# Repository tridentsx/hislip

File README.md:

# hislip

A native Go implementation of HiSLIP, the IVI High-Speed LAN Instrument
Protocol, for the [GoTMC][gotmc] test and measurement stack.

HiSLIP is specified by [IVI-6.1][ivi61], revision 2.0. It is the LXI-era
replacement for VXI-11 and requires no ONC/Sun RPC.

## Status

Early development. Milestone 0 of the design specification, the protocol codec,
is implemented and its exit criterion is met: the decoder is fuzzed, and the
data path is asserted to perform no heap allocation.

The server is next, before the client. That inverts the milestone numbering
deliberately — no HiSLIP-capable instrument is available on the development
bench, so a finished client would have nothing to talk to, whereas a finished
server can be driven immediately by NI-VISA, Keysight IO Libraries, pyvisa-py
and `lxi-tools/libhislip`. The reasoning is recorded under "Execution order" in
Part IV of the specification.

Conformance is established against independent implementations rather than
against this project's own two halves, which would agree with each other whether
or not they agree with IVI-6.1.

The design specification lives at
[docs/design-spec.md in tridentsx/tmc-gateway][design-spec], since it is a
single document covering this library (Part I), the PoE-to-GPIB adapter
hardware (Part II), and its TinyGo firmware (Part III) together, plus
milestones/acceptance-criteria/risk sections that cut across all three —
splitting it would have broken that traceability. Section references in this
repository's source comments, such as "§5.1", refer to it there. The hardware
design and firmware themselves also moved to `tmc-gateway`, along with the
KiCad netlist-verification tooling that supports them; this repository is now
the library alone.

This repository lives at `github.com/tridentsx/hislip` for now, not yet part
of the `gotmc` organisation. It was originally developed against the module
path `github.com/gotmc/hislip` on the assumption that no upstream repository
would need to exist yet — but a module's declared path has to match where
it's actually fetched from for `go get` to work at all, so it's renamed here
to the path it's really hosted at. The intent to offer this to `gotmc` once
it's finished hasn't changed; that will mean one real import-path rewrite
when/if it happens, not zero.

## Layout

```text
protocol/          wire format: header codec, message types, error codes,
                   MessageID arithmetic, version negotiation
server/            session state machine and the Device interface
client/            desktop client
extension/gotmc/   optional vendor extension for explicit reads
```

The `protocol` and `server` packages are the device side. They compile under
TinyGo for microcontroller firmware, which imposes two rules:

- imports are restricted to a small, verified subset of the standard library;
- the caller supplies every buffer, and the data path does not allocate.

Both rules exist because the same code runs on a Raspberry Pi RP2350 with a
cooperatively scheduled runtime and a stop-the-world garbage collector, where an
allocation in the data path can stall a timing-sensitive bus transfer.

The import boundary is enforced rather than merely documented. `TestDeviceImportGraph`
in the root package walks the transitive import graph of the device-side
packages and fails on anything outside an allowlist. The realistic failure is
not a deliberate bad import but an `fmt.Errorf` added to an error path long
after the boundary was agreed.

## Two rules worth knowing before reading the code

**Never size a buffer from the wire.** The header's payload length field is 64
bits wide and is supplied by the peer. `make([]byte, header.Length)` is a
denial-of-service vector on an unauthenticated TCP port. Use
`protocol.CheckLength` against the negotiated maximum, then stream through a
fixed scratch buffer with `protocol.ReadPayload`.

**Decoding is permissive on purpose.** `protocol.DecodeHeader` validates the
prologue and nothing else. A receiver has to be able to decode a header it
intends to reject, so that it can consume the payload and stay synchronised with
the peer. Acceptance decisions belong to the session layer, using
`MessageType.Defined`, `MessageType.Reserved`, `MessageType.LegalOn`,
`MessageType.MinVersion` and `CheckLength`.

## Testing

```sh
go test ./...
go test ./... -race -cover
go test ./protocol -run '^$' -fuzz=FuzzDecodeHeader -fuzztime=60s
```

Conformance vectors live in [internal/vectors](internal/vectors) as data files
rather than as Go literals, so that the same corpus can drive a firmware test
harness or an implementation in another language. They are written out by hand
from IVI-6.1, never generated by the code under test, so a coding error in the
codec cannot be masked by the same error in the expectation. The message type
table is transcribed twice for the same reason — once in
`protocol/constants.go` and once in `protocol/constants_test.go` — so that a
transcription error has to be made identically in both places to go unnoticed.

Three fuzz targets cover the decoder, the payload reader and the message
framing. `FuzzDecodeHeader` checks more than the absence of panics: any input
that decodes successfully must re-encode to exactly the bytes it came from,
which is what catches a wrong field offset or a byte-order mistake that a fixed
set of vectors can miss.

`TestCodecDoesNotAllocate` asserts that the data path performs no heap
allocation. This is a timing requirement rather than a memory one. The same code
runs on an RP2350 whose garbage collector stops both cores, so an allocation
during a transfer can stall a GPIB handshake, and a spurious handshake timeout
presents to the user as a bus fault. The assertions are excluded from race
builds, because the race detector allocates on its own account.

## Interoperability

Unit tests confirm the implementation does what its author intended. Only an
independent implementation confirms the intention was right, so conformance is
established against clients this project did not write:

```sh
./interop/run.sh
```

Three independent clients currently drive the example server — pyvisa-py,
PyHiSLIP and `lxi-tools/libhislip` — for 32 checks with no failures. Clients that
are not installed are skipped rather than failed.

Between them they have found three defects that a full unit suite did not, and
they settled the one open protocol question in the design specification: IVI-6.1
Table 4 lists `DeviceClearAcknowledge` on the asynchronous channel, and two
independent clients read it from the synchronous one, agreeing with the
transaction description instead.

Coverage, procedure, findings and the limitations of each client are recorded in
[interop/README.md](interop/README.md).

## A defect in IVI-6.1

Table 4 lists `DeviceClearAcknowledge`, message type 9, as an asynchronous
message. The Device Clear transaction description in section 6.12 contradicts
this: step 7 of the client procedure reads "Wait for the server to respond with
DeviceClearAcknowledge on the synchronous channel", and the message summary
table also gives the channel as synchronous.

This implementation follows the transaction description and treats the message
as synchronous. See `TestDeviceClearAcknowledgeChannel`. The intent is to
confirm the behaviour against independent third-party HiSLIP clients before the
server is released.

## Licence

MIT. See [LICENSE.txt](LICENSE.txt).

[design-spec]: https://github.com/tridentsx/tmc-gateway/blob/main/docs/design-spec.md
[gotmc]: https://github.com/gotmc
[ivi61]: https://www.ivifoundation.org/downloads/Protocol%20Specifications/IVI-6.1_HiSLIP-2.0-2020-04-23.pdf

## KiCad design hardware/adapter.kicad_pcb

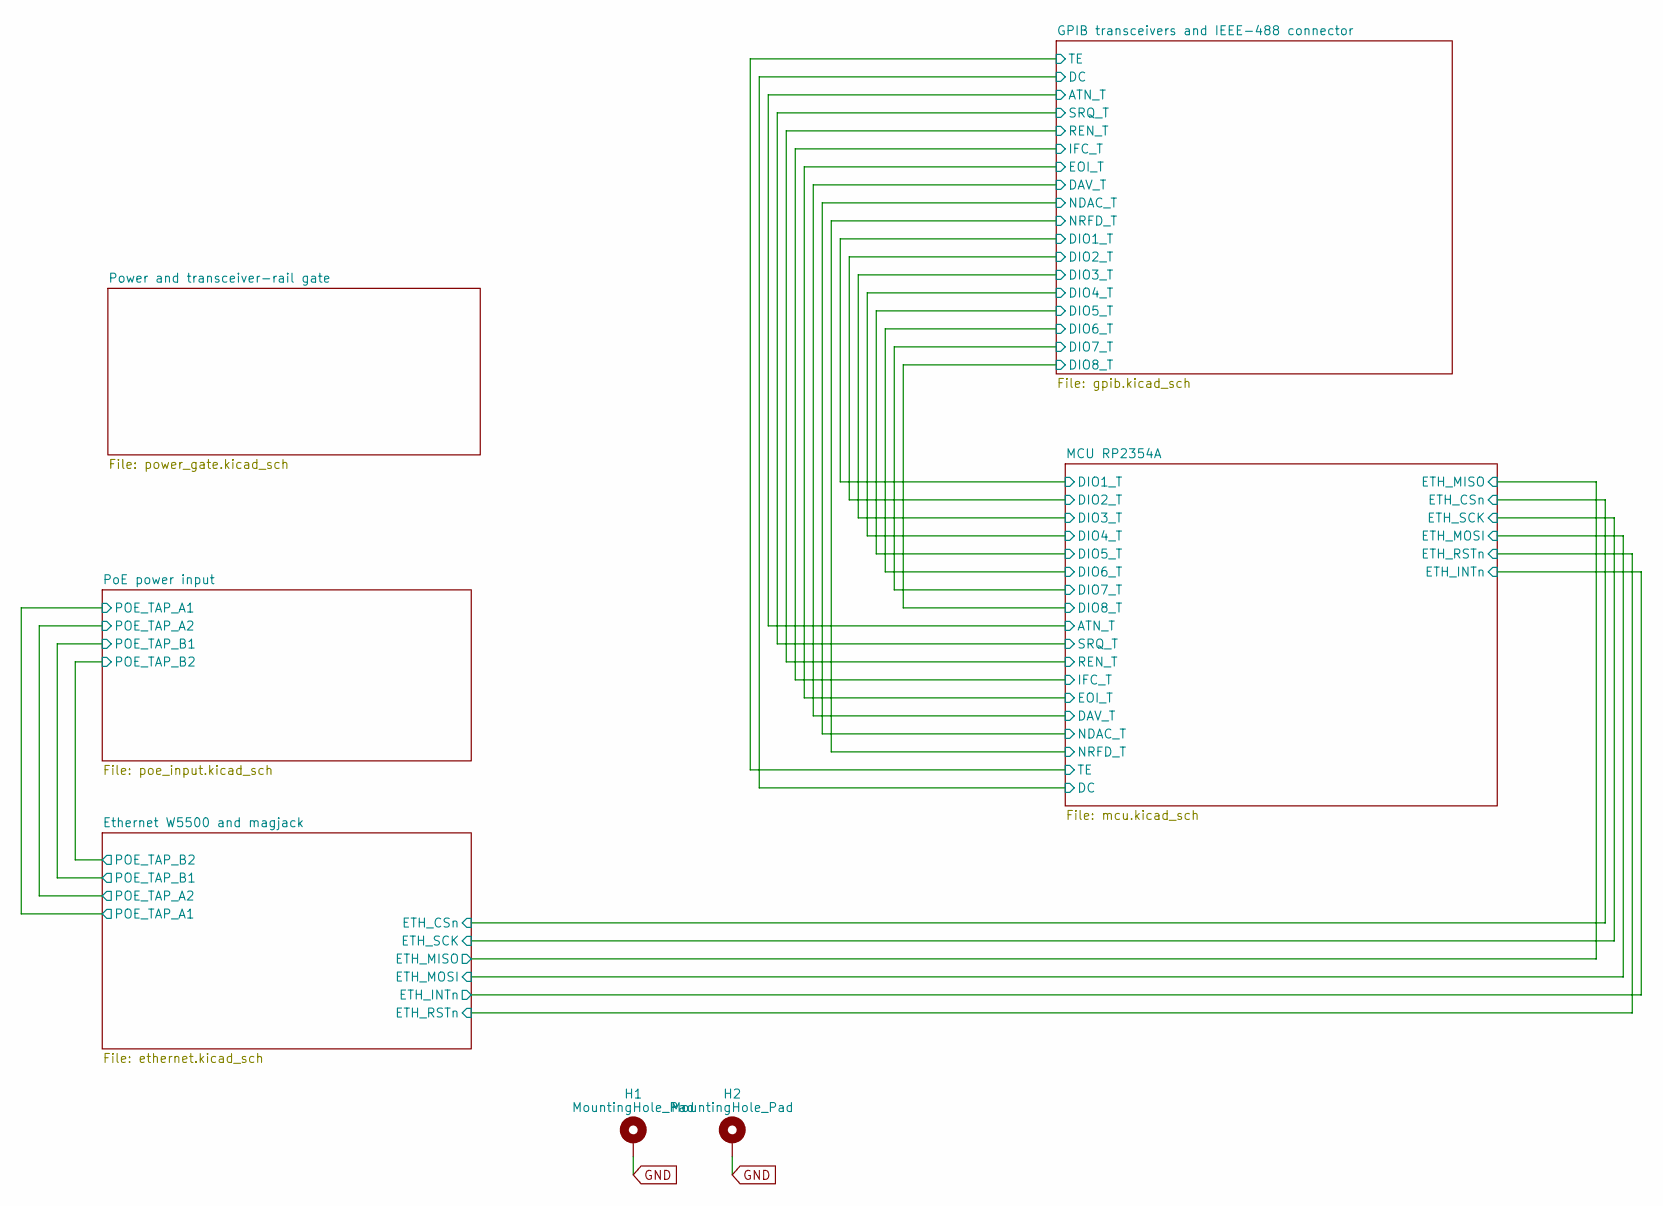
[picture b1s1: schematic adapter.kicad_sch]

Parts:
H1, H2: MountingHole_Pad; MountingHole_3.2mm_M3_Pad

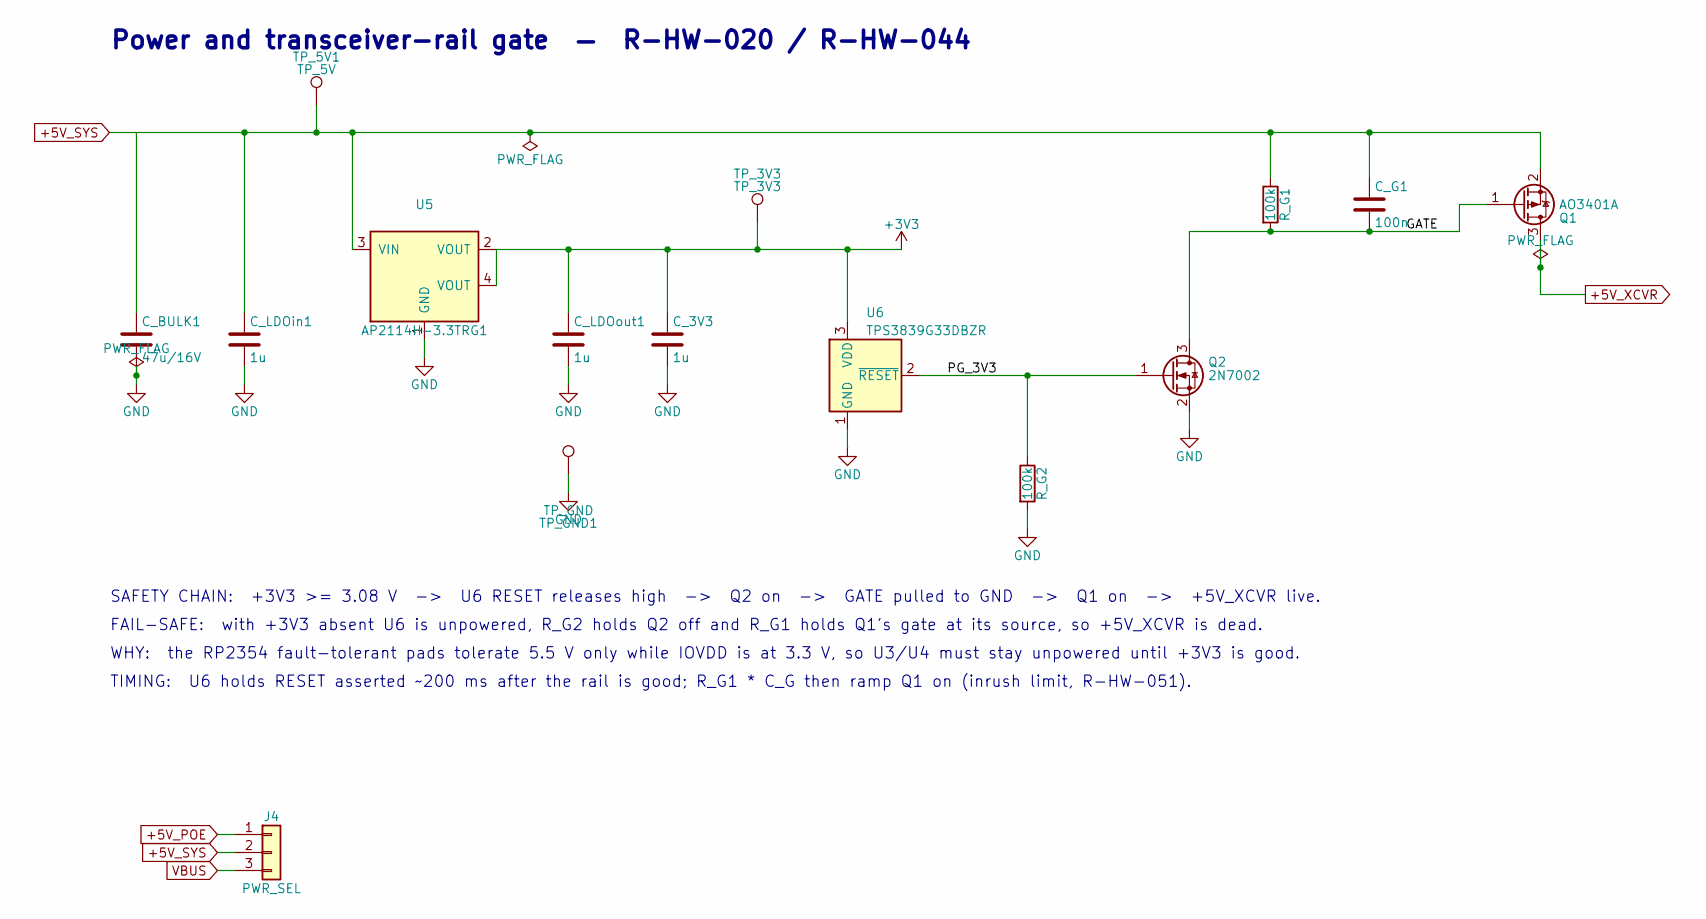
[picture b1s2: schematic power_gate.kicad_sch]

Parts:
C_3V3: 1u; C_0805_2012Metric
C_BULK1: 47u/16V; C_1206_3216Metric
C_G1: 100n; C_0805_2012Metric
C_LDOin1: 1u; C_0805_2012Metric
C_LDOout1: 1u; C_0805_2012Metric
J4: PWR_SEL; PinHeader_1x03_P2.54mm_Vertical
Q1: AO3401A; SOT-23
Q2: 2N7002; SOT-23
R_G1, R_G2: 100k; R_0805_2012Metric
TP_3V3: TP_3V3; TestPoint_Pad_D1.5mm
TP_5V1: TP_5V; TestPoint_Pad_D1.5mm
TP_GND1: TP_GND; TestPoint_Pad_D1.5mm
U5: AP2114H-3.3TRG1; SOT-223_L6.7-W3.5-P2.30-BR
U6: TPS3839G33DBZR; SOT-23

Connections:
+3V3: C_3V3.1, C_LDOout1.1, TP_3V3.1 (1_1), U5.2 (VOUT), U5.4 (VOUT), U6.3 (VDD); also elsewhere on the board
+5V_POE: J4.1; also elsewhere on the board
/Power and transceiver-rail gate/GATE: C_G1.2, Q1.1 (G), Q2.3 (D), R_G1.2
/Power and transceiver-rail gate/PG_3V3: Q2.1 (G), R_G2.1, U6.2 (~RESET)
VBUS: J4.3; also elsewhere on the board

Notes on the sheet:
FAIL-SAFE: with +3V3 absent U6 is unpowered, R_G2 holds Q2 off and R_G1 holds Q1's gate at its source, so +5V_XCVR is dead.
SAFETY CHAIN: +3V3 >= 3.08 V -> U6 RESET releases high -> Q2 on -> GATE pulled to GND -> Q1 on -> +5V_XCVR live.
TIMING: U6 holds RESET asserted ~200 ms after the rail is good; R_G1 * C_G then ramp Q1 on (inrush limit, R-HW-051).
WHY: the RP2354 fault-tolerant pads tolerate 5.5 V only while IOVDD is at 3.3 V, so U3/U4 must stay unpowered until +3V3 is good.
Power and transceiver-rail gate — R-HW-020 / R-HW-044

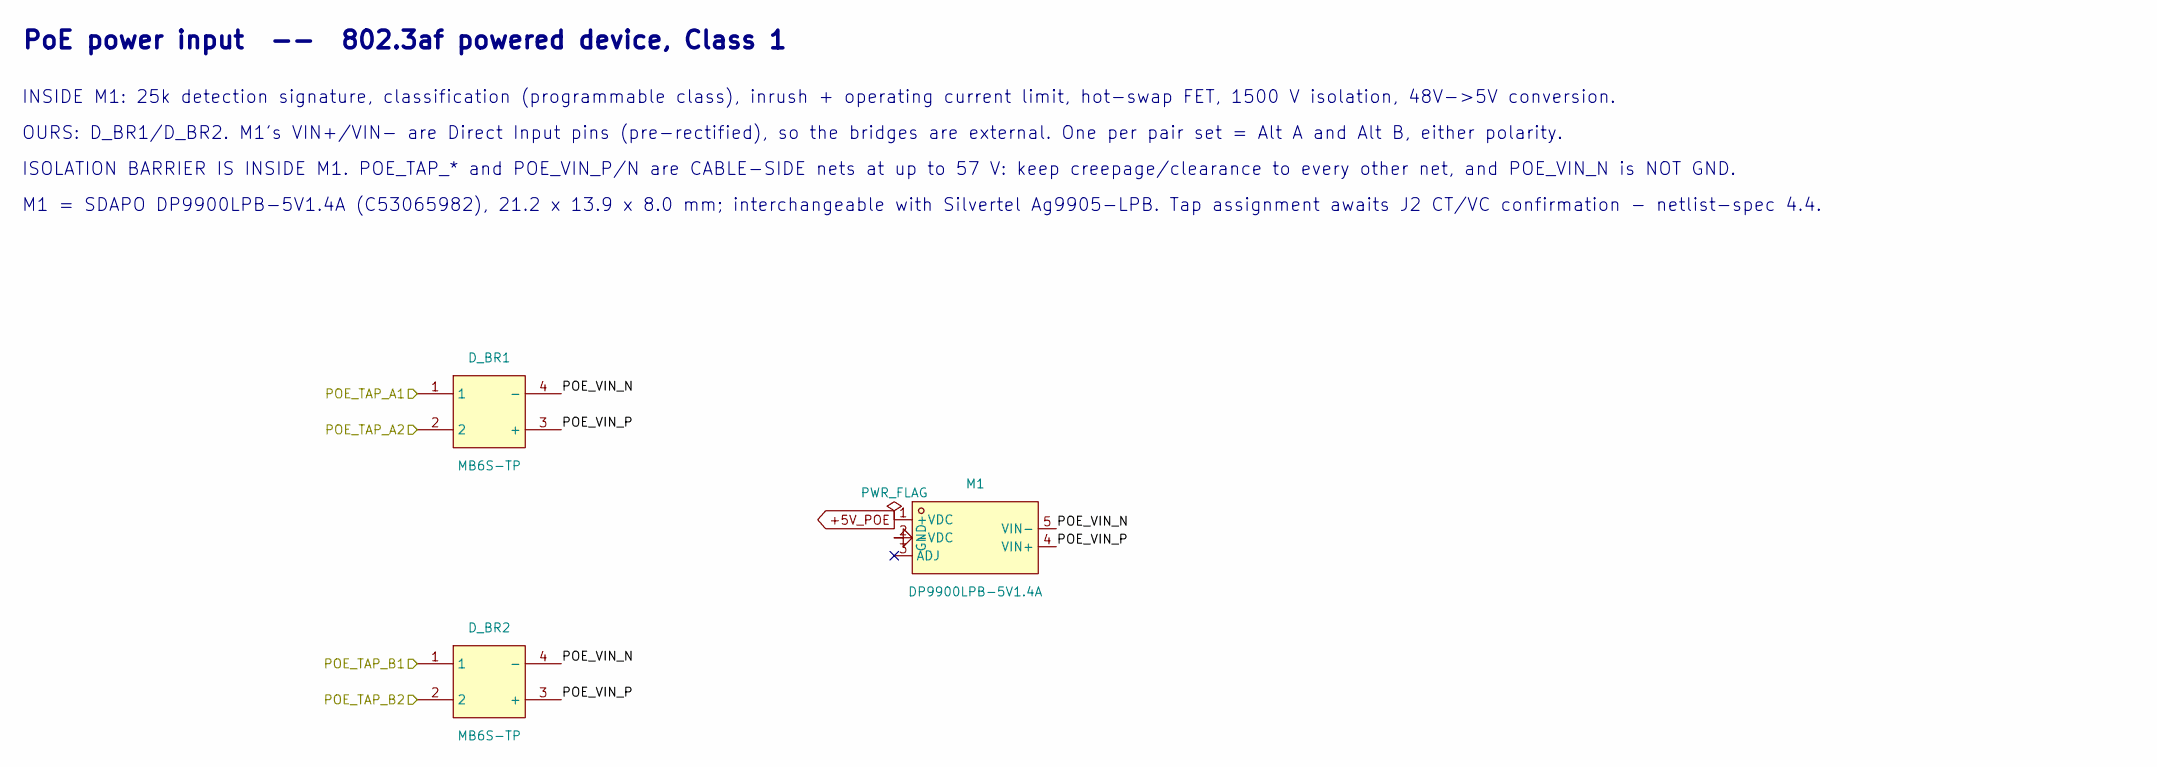
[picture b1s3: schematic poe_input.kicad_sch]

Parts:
D_BR1, D_BR2: MB6S-TP; MBS_L4.7-W4.0-P2.50-LS7.0-TL
M1: DP9900LPB-5V1.4A; COMM-SMD_DP9900LPB-5V1.4A

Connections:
+5V_POE: M1.1 (+VDC); also elsewhere on the board
/Ethernet W5500 and magjack/POE_TAP_A1: D_BR1.1; also elsewhere on the board
/Ethernet W5500 and magjack/POE_TAP_A2: D_BR1.2; also elsewhere on the board
/Ethernet W5500 and magjack/POE_TAP_B1: D_BR2.1; also elsewhere on the board
/Ethernet W5500 and magjack/POE_TAP_B2: D_BR2.2; also elsewhere on the board
/PoE power input/POE_VIN_N: D_BR1.4 (-), D_BR2.4 (-), M1.5 (VIN-)
/PoE power input/POE_VIN_P: D_BR1.3 (+), D_BR2.3 (+), M1.4 (VIN+)

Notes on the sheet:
OURS: D_BR1/D_BR2. M1's VIN+/VIN- are Direct Input pins (pre-rectified), so the bridges are external. One per pair set = Alt A and Alt B, either polarity.
ISOLATION BARRIER IS INSIDE M1. POE_TAP_* and POE_VIN_P/N are CABLE-SIDE nets at up to 57 V: keep creepage/clearance to every other net, and POE_VIN_N is NOT GND.
M1 = SDAPO DP9900LPB-5V1.4A (C53065982), 21.2 x 13.9 x 8.0 mm; interchangeable with Silvertel Ag9905-LPB. Tap assignment awaits J2 CT/VC confirmation - netlist-spec 4.4.
INSIDE M1: 25k detection signature, classification (programmable class), inrush + operating current limit, hot-swap FET, 1500 V isolation, 48V->5V conversion.
PoE power input -- 802.3af powered device, Class 1

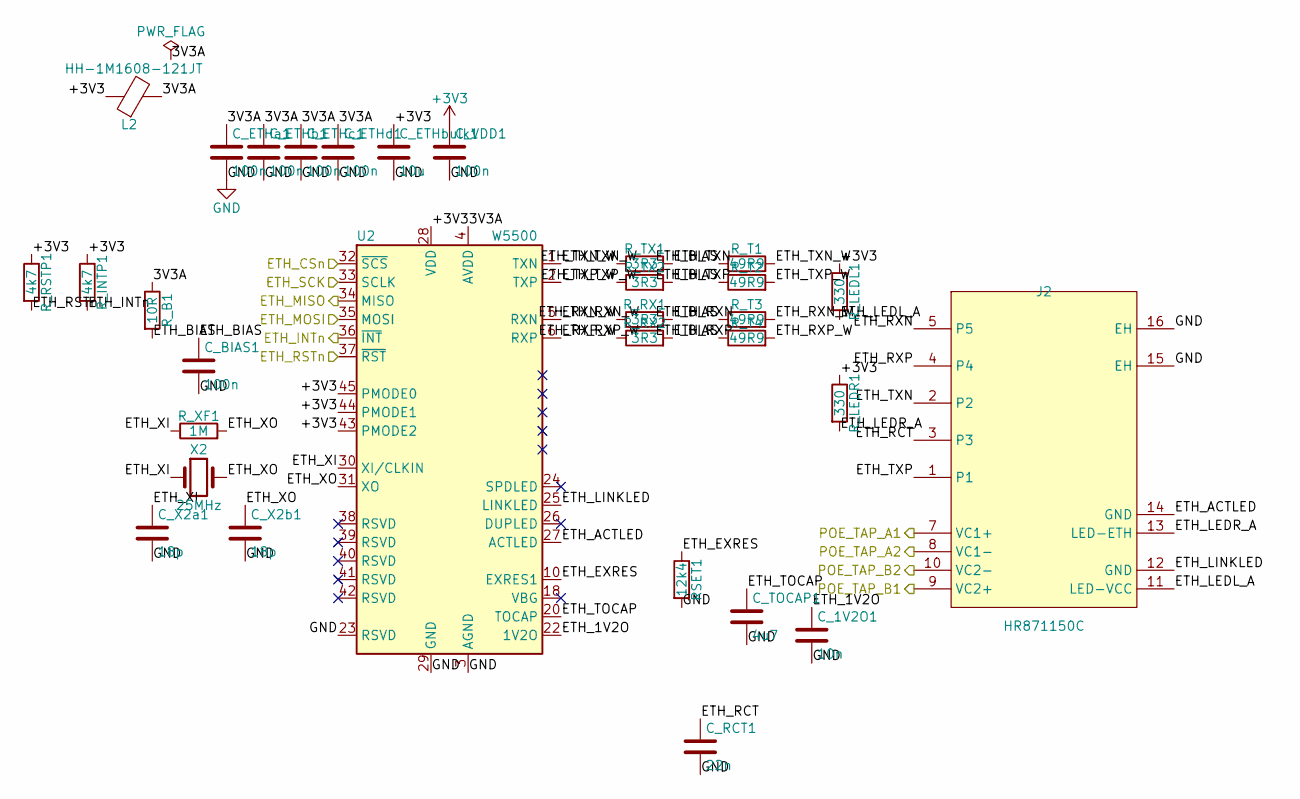
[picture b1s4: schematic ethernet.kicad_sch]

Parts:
C_1V2O1: 10n; C_0805_2012Metric
C_BIAS1: 100n; C_0805_2012Metric
C_ETHa1: 100n; C_0805_2012Metric
C_ETHb1: 100n; C_0805_2012Metric
C_ETHbulk1: 10u; C_0805_2012Metric
C_ETHc1: 100n; C_0805_2012Metric
C_ETHd1: 100n; C_0805_2012Metric
C_RCT1: 22n; C_0805_2012Metric
C_TOCAP1: 4u7; C_0805_2012Metric
C_VDD1: 100n; C_0805_2012Metric
C_X2a1, C_X2b1: 18p; C_0805_2012Metric
J2: HR871150C; RJ45-TH_HR871150C
L2: HH-1M1608-121JT; L_0603_1608Metric
RSET1: 12k4; R_0805_2012Metric
R_B1: 10R; R_0805_2012Metric
R_INTP1: 4k7; R_0805_2012Metric
R_LEDL1: 330; R_0805_2012Metric
R_LEDR1: 330; R_0805_2012Metric
R_RSTP1: 4k7; R_0805_2012Metric
R_RX1, R_RX2: 3R3; R_0805_2012Metric
R_T1, R_T2, R_T3, R_T4: 49R9; R_0805_2012Metric
R_TX1, R_TX2: 3R3; R_0805_2012Metric
R_XF1: 1M; R_0805_2012Metric
U2: W5500; LQFP-48_7x7mm_P0.5mm
X2: 25MHz; Crystal_SMD_3225-4Pin_3.2x2.5mm

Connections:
+3V3: C_ETHbulk1.1, C_VDD1.1, L2.1, R_INTP1.1, R_LEDL1.1, R_LEDR1.1, R_RSTP1.1, U2.28 (VDD), U2.43 (PMODE2), U2.44 (PMODE1), U2.45 (PMODE0); also elsewhere on the board
/Ethernet W5500 and magjack/3V3A: C_ETHa1.1, C_ETHb1.1, C_ETHc1.1, C_ETHd1.1, L2.2, R_B1.1, U2.4 (AVDD), U2.8 (AVDD), U2.11 (AVDD), U2.15 (AVDD), U2.17 (AVDD), U2.21 (AVDD)
/Ethernet W5500 and magjack/ETH_1V2O: C_1V2O1.1, U2.22 (1V2O)
/Ethernet W5500 and magjack/ETH_ACTLED: J2.14 (GND), U2.27 (ACTLED)
/Ethernet W5500 and magjack/ETH_BIAS: C_BIAS1.1, R_B1.2, R_T1.1, R_T2.1, R_T3.1, R_T4.1
/Ethernet W5500 and magjack/ETH_CSn: U2.32 (~SCS); also elsewhere on the board
/Ethernet W5500 and magjack/ETH_EXRES: RSET1.1, U2.10 (EXRES1)
/Ethernet W5500 and magjack/ETH_INTn: R_INTP1.2, U2.36 (~INT); also elsewhere on the board
/Ethernet W5500 and magjack/ETH_LEDL_A: J2.11 (LED-VCC), R_LEDL1.2
/Ethernet W5500 and magjack/ETH_LEDR_A: J2.13 (LED-ETH), R_LEDR1.2
/Ethernet W5500 and magjack/ETH_LINKLED: J2.12 (GND), U2.25 (LINKLED)
/Ethernet W5500 and magjack/ETH_MISO: U2.34 (MISO); also elsewhere on the board
/Ethernet W5500 and magjack/ETH_MOSI: U2.35 (MOSI); also elsewhere on the board
/Ethernet W5500 and magjack/ETH_RCT: C_RCT1.1, J2.3
/Ethernet W5500 and magjack/ETH_RSTn: R_RSTP1.2, U2.37 (~RST); also elsewhere on the board
/Ethernet W5500 and magjack/ETH_RXN: J2.5, R_RX1.2
/Ethernet W5500 and magjack/ETH_RXN_W: R_RX1.1, R_T3.2, U2.5 (RXN)
/Ethernet W5500 and magjack/ETH_RXP: J2.4, R_RX2.2
/Ethernet W5500 and magjack/ETH_RXP_W: R_RX2.1, R_T4.2, U2.6 (RXP)
/Ethernet W5500 and magjack/ETH_SCK: U2.33 (SCLK); also elsewhere on the board
/Ethernet W5500 and magjack/ETH_TOCAP: C_TOCAP1.1, U2.20 (TOCAP)
/Ethernet W5500 and magjack/ETH_TXN: J2.2, R_TX1.2
/Ethernet W5500 and magjack/ETH_TXN_W: R_T1.2, R_TX1.1, U2.1 (TXN)
/Ethernet W5500 and magjack/ETH_TXP: J2.1, R_TX2.2
/Ethernet W5500 and magjack/ETH_TXP_W: R_T2.2, R_TX2.1, U2.2 (TXP)
/Ethernet W5500 and magjack/ETH_XI: C_X2a1.1, R_XF1.1, U2.30 (XI/CLKIN), X2.1
/Ethernet W5500 and magjack/ETH_XO: C_X2b1.1, R_XF1.2, U2.31 (XO), X2.2
/Ethernet W5500 and magjack/POE_TAP_A1: J2.7 (VC1+); also elsewhere on the board
/Ethernet W5500 and magjack/POE_TAP_A2: J2.8 (VC1-); also elsewhere on the board
/Ethernet W5500 and magjack/POE_TAP_B1: J2.9 (VC2+); also elsewhere on the board
/Ethernet W5500 and magjack/POE_TAP_B2: J2.10 (VC2-); also elsewhere on the board

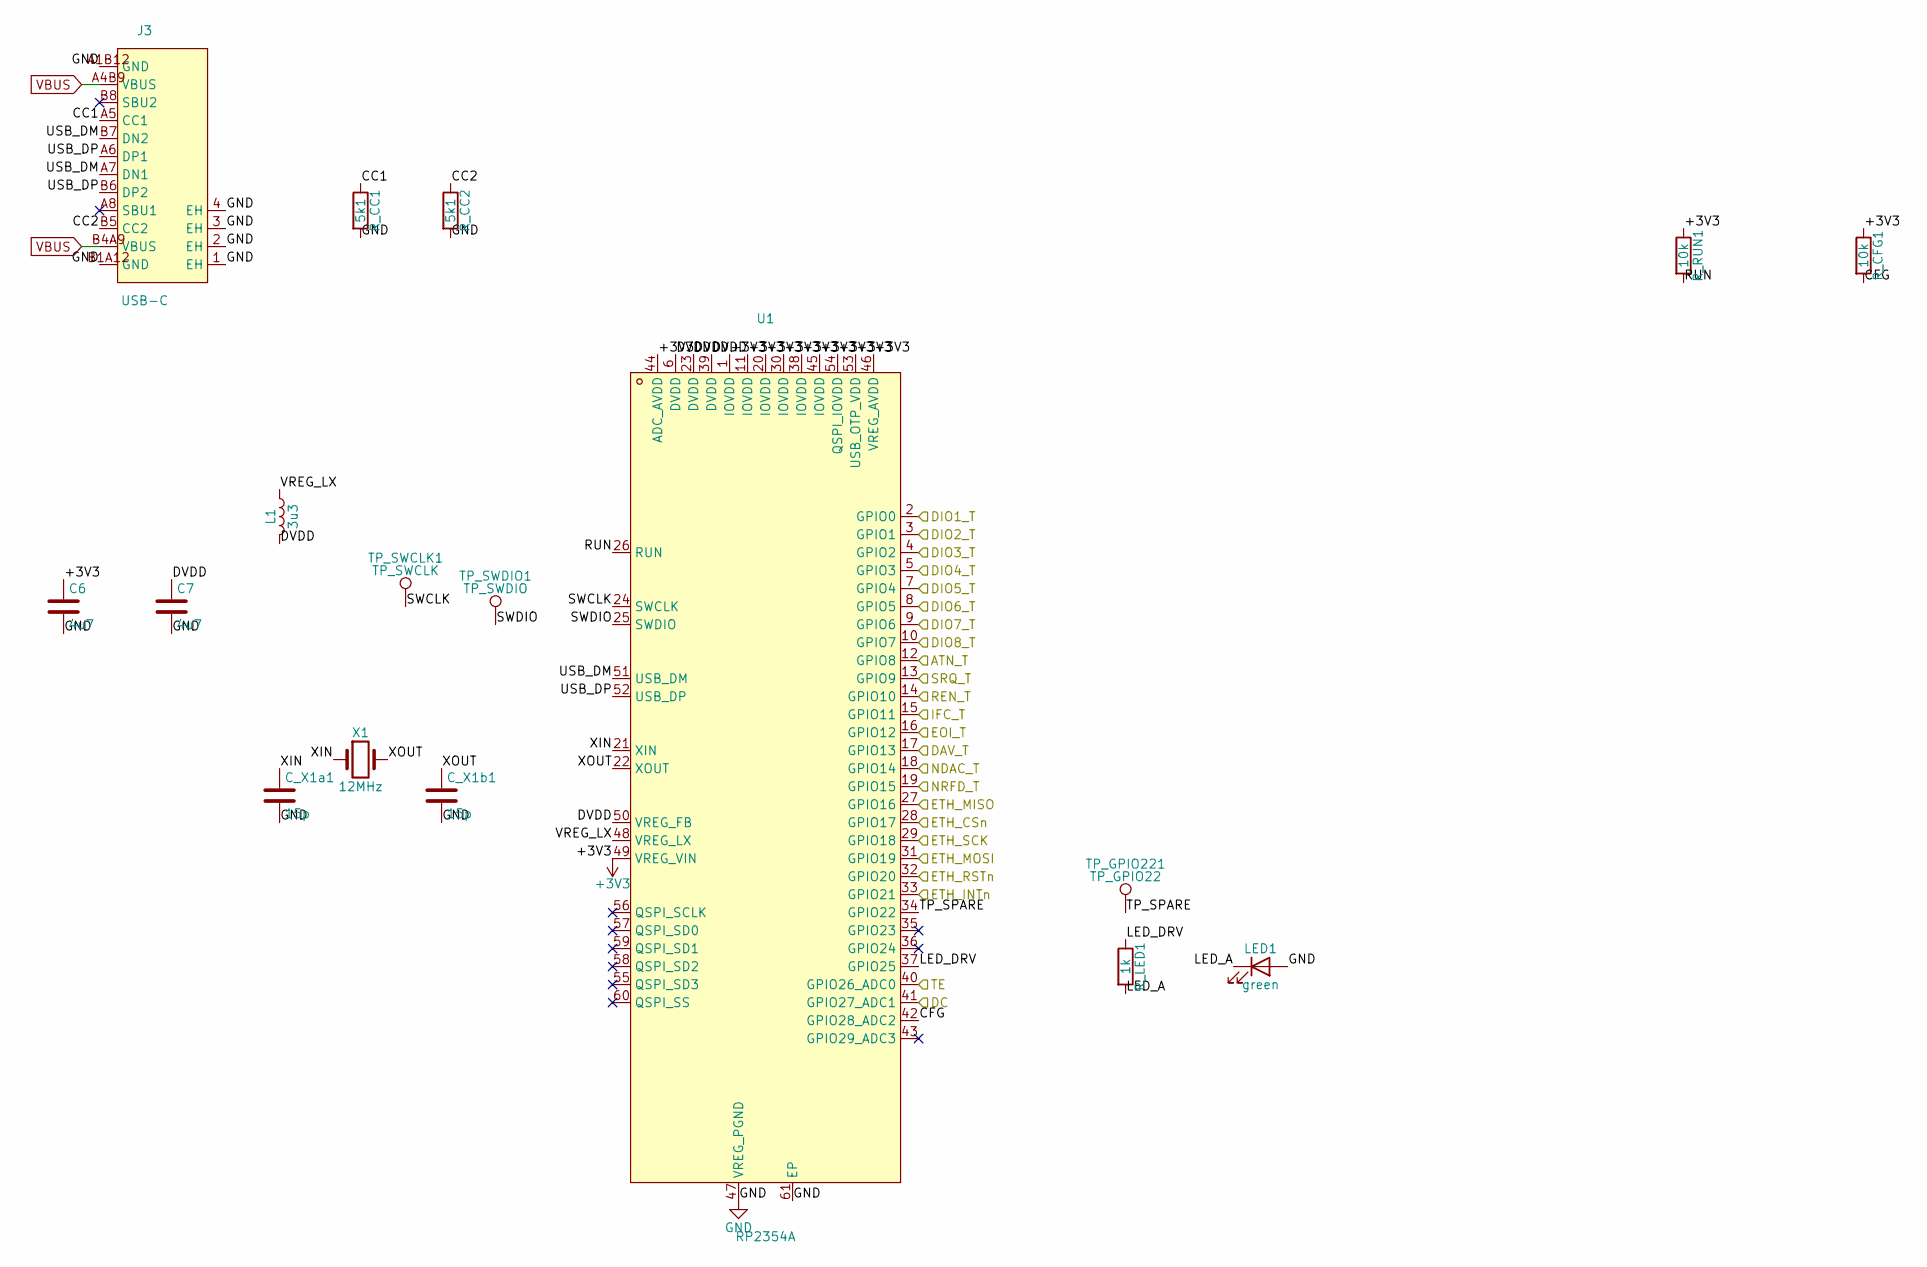
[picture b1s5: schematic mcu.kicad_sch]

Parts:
C6, C7: 4u7; C_0805_2012Metric
C_X1a1, C_X1b1: 15p; C_0805_2012Metric
J3: USB-C; USB-C_SMD-TYPE-C-31-M-12_1
L1: 3u3; L_0805_2012Metric
LED1: green; LED_0805_2012Metric
R_CC1, R_CC2: 5k1; R_0805_2012Metric
R_CFG1: 10k; R_0805_2012Metric
R_LED1: 1k; R_0805_2012Metric
R_RUN1: 10k; R_0805_2012Metric
TP_GPIO221: TP_GPIO22; TestPoint_Pad_D1.5mm
TP_SWCLK1: TP_SWCLK; TestPoint_Pad_D1.5mm
TP_SWDIO1: TP_SWDIO; TestPoint_Pad_D1.5mm
U1: RP2354A; QFN-60_L7.0-W7.0-P0.40-TL-EP3.4
X1: 12MHz; Crystal_SMD_3225-4Pin_3.2x2.5mm

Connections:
+3V3: C6.1, R_CFG1.1, R_RUN1.1, U1.1 (IOVDD), U1.11 (IOVDD), U1.20 (IOVDD), U1.30 (IOVDD), U1.38 (IOVDD), U1.44 (ADC_AVDD), U1.45 (IOVDD), U1.46 (VREG_AVDD), U1.49 (VREG_VIN), U1.53 (USB_OTP_VDD), U1.54 (QSPI_IOVDD); also elsewhere on the board
/Ethernet W5500 and magjack/ETH_CSn: U1.28 (GPIO17); also elsewhere on the board
/Ethernet W5500 and magjack/ETH_INTn: U1.33 (GPIO21); also elsewhere on the board
/Ethernet W5500 and magjack/ETH_MISO: U1.27 (GPIO16); also elsewhere on the board
/Ethernet W5500 and magjack/ETH_MOSI: U1.31 (GPIO19); also elsewhere on the board
/Ethernet W5500 and magjack/ETH_RSTn: U1.32 (GPIO20); also elsewhere on the board
/Ethernet W5500 and magjack/ETH_SCK: U1.29 (GPIO18); also elsewhere on the board
/GPIB transceivers and IEEE-488 connector/ATN_T: U1.12 (GPIO8); also elsewhere on the board
/GPIB transceivers and IEEE-488 connector/DAV_T: U1.17 (GPIO13); also elsewhere on the board
/GPIB transceivers and IEEE-488 connector/DC: U1.41 (GPIO27_ADC1); also elsewhere on the board
/GPIB transceivers and IEEE-488 connector/DIO1_T: U1.2 (GPIO0); also elsewhere on the board
/GPIB transceivers and IEEE-488 connector/DIO2_T: U1.3 (GPIO1); also elsewhere on the board
/GPIB transceivers and IEEE-488 connector/DIO3_T: U1.4 (GPIO2); also elsewhere on the board
/GPIB transceivers and IEEE-488 connector/DIO4_T: U1.5 (GPIO3); also elsewhere on the board
/GPIB transceivers and IEEE-488 connector/DIO5_T: U1.7 (GPIO4); also elsewhere on the board
/GPIB transceivers and IEEE-488 connector/DIO6_T: U1.8 (GPIO5); also elsewhere on the board
/GPIB transceivers and IEEE-488 connector/DIO7_T: U1.9 (GPIO6); also elsewhere on the board
/GPIB transceivers and IEEE-488 connector/DIO8_T: U1.10 (GPIO7); also elsewhere on the board
/GPIB transceivers and IEEE-488 connector/EOI_T: U1.16 (GPIO12); also elsewhere on the board
/GPIB transceivers and IEEE-488 connector/IFC_T: U1.15 (GPIO11); also elsewhere on the board
/GPIB transceivers and IEEE-488 connector/NDAC_T: U1.18 (GPIO14); also elsewhere on the board
/GPIB transceivers and IEEE-488 connector/NRFD_T: U1.19 (GPIO15); also elsewhere on the board
/GPIB transceivers and IEEE-488 connector/REN_T: U1.14 (GPIO10); also elsewhere on the board
/GPIB transceivers and IEEE-488 connector/SRQ_T: U1.13 (GPIO9); also elsewhere on the board
/GPIB transceivers and IEEE-488 connector/TE: U1.40 (GPIO26_ADC0); also elsewhere on the board
/MCU RP2354A/CC1: J3.A5 (CC1), R_CC1.1
/MCU RP2354A/CC2: J3.B5 (CC2), R_CC2.1
/MCU RP2354A/CFG: R_CFG1.2, U1.42 (GPIO28_ADC2)
/MCU RP2354A/DVDD: C7.1, L1.2, U1.6 (DVDD), U1.23 (DVDD), U1.39 (DVDD), U1.50 (VREG_FB)
/MCU RP2354A/LED_A: LED1.1 (K), R_LED1.2
/MCU RP2354A/LED_DRV: R_LED1.1, U1.37 (GPIO25)
/MCU RP2354A/RUN: R_RUN1.2, U1.26 (RUN)
/MCU RP2354A/SWCLK: TP_SWCLK1.1 (1_1), U1.24 (SWCLK)
/MCU RP2354A/SWDIO: TP_SWDIO1.1 (1_1), U1.25 (SWDIO)
/MCU RP2354A/TP_SPARE: TP_GPIO221.1 (1_1), U1.34 (GPIO22)
/MCU RP2354A/USB_DM: J3.A7 (DN1), J3.B7 (DN2), U1.51 (USB_DM)
/MCU RP2354A/USB_DP: J3.A6 (DP1), J3.B6 (DP2), U1.52 (USB_DP)
/MCU RP2354A/VREG_LX: L1.1, U1.48 (VREG_LX)
/MCU RP2354A/XIN: C_X1a1.1, U1.21 (XIN), X1.1
/MCU RP2354A/XOUT: C_X1b1.1, U1.22 (XOUT), X1.2
VBUS: J3.A4B9 (VBUS), J3.B4A9 (VBUS); also elsewhere on the board

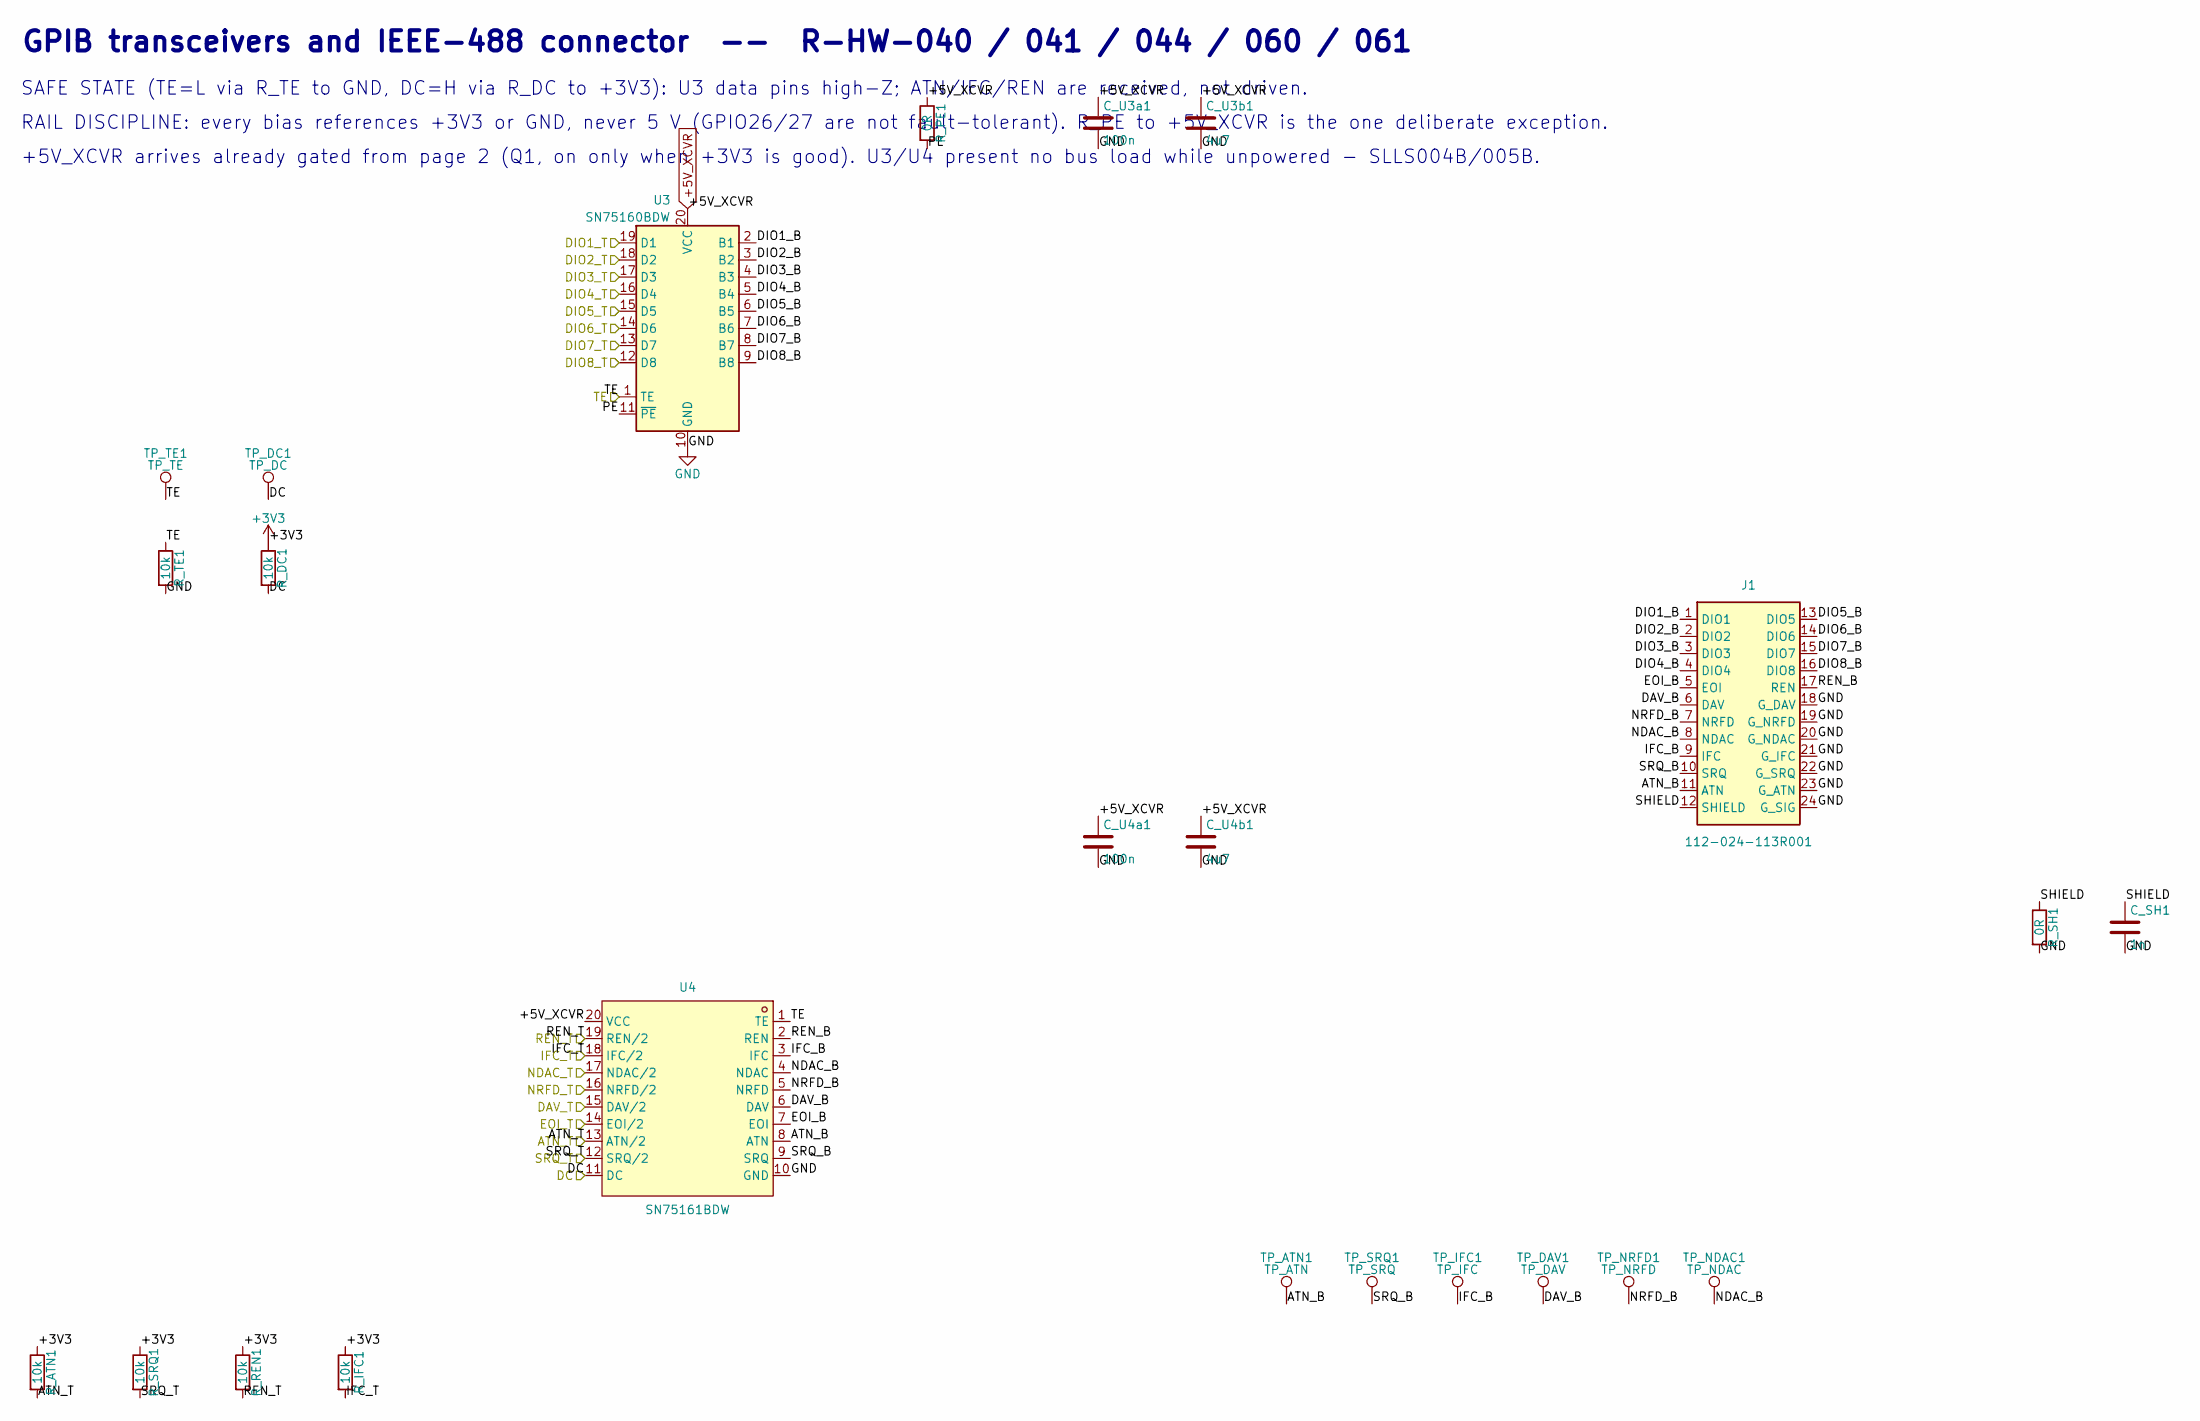
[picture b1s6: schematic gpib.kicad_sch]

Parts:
C_SH1: 1n; C_0805_2012Metric
C_U3a1, C_U4a1: 100n; C_0805_2012Metric
C_U3b1, C_U4b1: 4u7; C_0805_2012Metric
J1: 112-024-113R001; CONN_112-024-113R001_NRC; MPN 112-024-113R001
R_ATN1: 10k; R_0805_2012Metric
R_DC1: 10k; R_0805_2012Metric
R_IFC1: 10k; R_0805_2012Metric
R_PE1: 0R; R_0805_2012Metric
R_REN1: 10k; R_0805_2012Metric
R_SH1: 0R; R_0805_2012Metric
R_SRQ1: 10k; R_0805_2012Metric
R_TE1: 10k; R_0805_2012Metric
TP_ATN1: TP_ATN; TestPoint_Pad_D1.5mm
TP_DAV1: TP_DAV; TestPoint_Pad_D1.5mm
TP_DC1: TP_DC; TestPoint_Pad_D1.5mm
TP_IFC1: TP_IFC; TestPoint_Pad_D1.5mm
TP_NDAC1: TP_NDAC; TestPoint_Pad_D1.5mm
TP_NRFD1: TP_NRFD; TestPoint_Pad_D1.5mm
TP_SRQ1: TP_SRQ; TestPoint_Pad_D1.5mm
TP_TE1: TP_TE; TestPoint_Pad_D1.5mm
U3: SN75160BDW; SOIC-20W_7.5x12.8mm_P1.27mm
U4: SN75161BDW; SOIC-20W_7.5x12.8mm_P1.27mm

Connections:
+3V3: R_ATN1.1, R_DC1.1, R_IFC1.1, R_REN1.1, R_SRQ1.1; also elsewhere on the board
/GPIB transceivers and IEEE-488 connector/ATN_B: J1.11 (ATN), TP_ATN1.1 (1_1), U4.8 (ATN)
/GPIB transceivers and IEEE-488 connector/ATN_T: R_ATN1.2, U4.13 (ATN/2); also elsewhere on the board
/GPIB transceivers and IEEE-488 connector/DAV_B: J1.6 (DAV), TP_DAV1.1 (1_1), U4.6 (DAV)
/GPIB transceivers and IEEE-488 connector/DAV_T: U4.15 (DAV/2); also elsewhere on the board
/GPIB transceivers and IEEE-488 connector/DC: R_DC1.2, TP_DC1.1 (1_1), U4.11 (DC); also elsewhere on the board
/GPIB transceivers and IEEE-488 connector/DIO1_B: J1.1 (DIO1), U3.2 (B1)
/GPIB transceivers and IEEE-488 connector/DIO1_T: U3.19 (D1); also elsewhere on the board
/GPIB transceivers and IEEE-488 connector/DIO2_B: J1.2 (DIO2), U3.3 (B2)
/GPIB transceivers and IEEE-488 connector/DIO2_T: U3.18 (D2); also elsewhere on the board
/GPIB transceivers and IEEE-488 connector/DIO3_B: J1.3 (DIO3), U3.4 (B3)
/GPIB transceivers and IEEE-488 connector/DIO3_T: U3.17 (D3); also elsewhere on the board
/GPIB transceivers and IEEE-488 connector/DIO4_B: J1.4 (DIO4), U3.5 (B4)
/GPIB transceivers and IEEE-488 connector/DIO4_T: U3.16 (D4); also elsewhere on the board
/GPIB transceivers and IEEE-488 connector/DIO5_B: J1.13 (DIO5), U3.6 (B5)
/GPIB transceivers and IEEE-488 connector/DIO5_T: U3.15 (D5); also elsewhere on the board
/GPIB transceivers and IEEE-488 connector/DIO6_B: J1.14 (DIO6), U3.7 (B6)
/GPIB transceivers and IEEE-488 connector/DIO6_T: U3.14 (D6); also elsewhere on the board
/GPIB transceivers and IEEE-488 connector/DIO7_B: J1.15 (DIO7), U3.8 (B7)
/GPIB transceivers and IEEE-488 connector/DIO7_T: U3.13 (D7); also elsewhere on the board
/GPIB transceivers and IEEE-488 connector/DIO8_B: J1.16 (DIO8), U3.9 (B8)
/GPIB transceivers and IEEE-488 connector/DIO8_T: U3.12 (D8); also elsewhere on the board
/GPIB transceivers and IEEE-488 connector/EOI_B: J1.5 (EOI), U4.7 (EOI)
/GPIB transceivers and IEEE-488 connector/EOI_T: U4.14 (EOI/2); also elsewhere on the board
/GPIB transceivers and IEEE-488 connector/IFC_B: J1.9 (IFC), TP_IFC1.1 (1_1), U4.3 (IFC)
/GPIB transceivers and IEEE-488 connector/IFC_T: R_IFC1.2, U4.18 (IFC/2); also elsewhere on the board
/GPIB transceivers and IEEE-488 connector/NDAC_B: J1.8 (NDAC), TP_NDAC1.1 (1_1), U4.4 (NDAC)
/GPIB transceivers and IEEE-488 connector/NDAC_T: U4.17 (NDAC/2); also elsewhere on the board
/GPIB transceivers and IEEE-488 connector/NRFD_B: J1.7 (NRFD), TP_NRFD1.1 (1_1), U4.5 (NRFD)
/GPIB transceivers and IEEE-488 connector/NRFD_T: U4.16 (NRFD/2); also elsewhere on the board
/GPIB transceivers and IEEE-488 connector/PE: R_PE1.2, U3.11 (~PE)
/GPIB transceivers and IEEE-488 connector/REN_B: J1.17 (REN), U4.2 (REN)
/GPIB transceivers and IEEE-488 connector/REN_T: R_REN1.2, U4.19 (REN/2); also elsewhere on the board
/GPIB transceivers and IEEE-488 connector/SHIELD: C_SH1.1, J1.12 (SHIELD), R_SH1.1
/GPIB transceivers and IEEE-488 connector/SRQ_B: J1.10 (SRQ), TP_SRQ1.1 (1_1), U4.9 (SRQ)
/GPIB transceivers and IEEE-488 connector/SRQ_T: R_SRQ1.2, U4.12 (SRQ/2); also elsewhere on the board
/GPIB transceivers and IEEE-488 connector/TE: R_TE1.1, TP_TE1.1 (1_1), U3.1 (TE), U4.1 (TE); also elsewhere on the board

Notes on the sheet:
RAIL DISCIPLINE: every bias references +3V3 or GND, never 5 V (GPIO26/27 are not fault-tolerant). R_PE to +5V_XCVR is the one deliberate exception.
+5V_XCVR arrives already gated from page 2 (Q1, on only when +3V3 is good). U3/U4 present no bus load while unpowered - SLLS004B/005B.
SAFE STATE (TE=L via R_TE to GND, DC=H via R_DC to +3V3): U3 data pins high-Z; ATN/IFC/REN are received, not driven.
GPIB transceivers and IEEE-488 connector -- R-HW-040 / 041 / 044 / 060 / 061

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
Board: 4 copper layers, 92 parts (70 on the bottom side), 91 nets, no tracks yet.
